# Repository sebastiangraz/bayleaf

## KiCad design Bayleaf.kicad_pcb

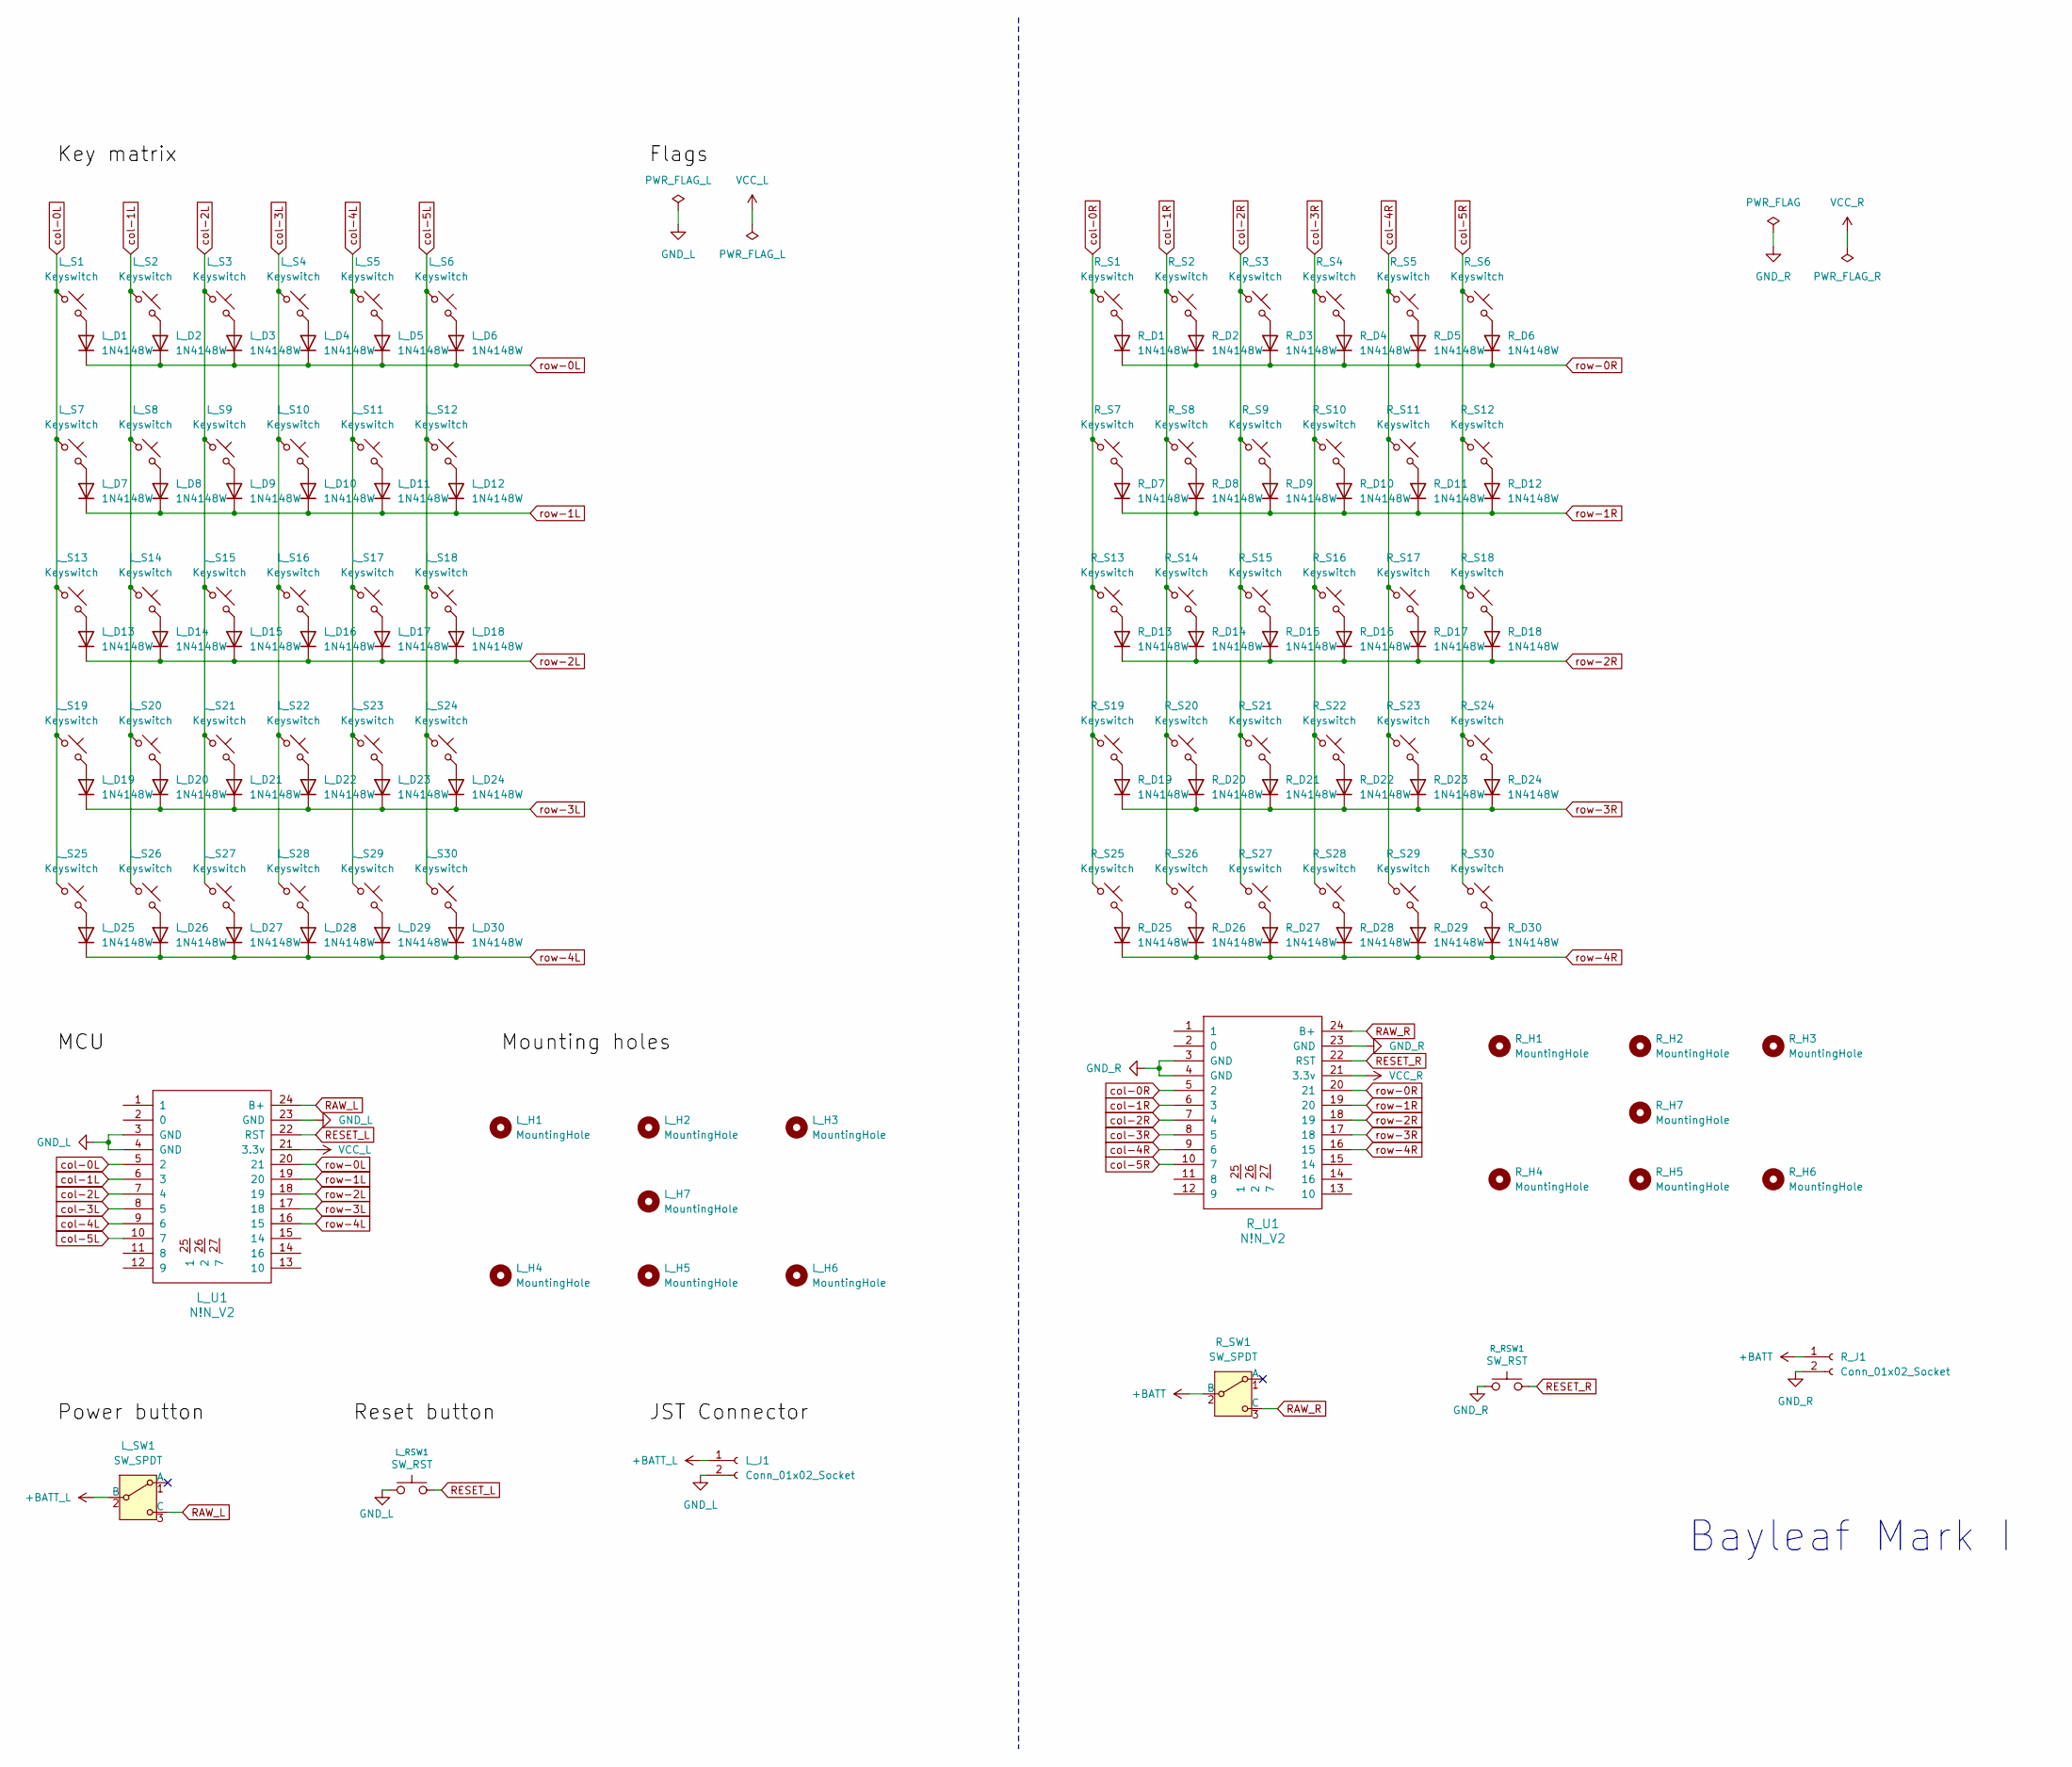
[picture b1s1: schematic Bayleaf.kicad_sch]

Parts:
L_D1, L_D2, L_D3, L_D4, L_D5, L_D6, L_D7, L_D8, L_D9, L_D10, L_D11, L_D12, L_D13, L_D14, L_D15, L_D16, L_D17, L_D18, L_D19, L_D20, L_D21, L_D22, L_D23, L_D24, L_D25, L_D26, L_D27, L_D28, L_D29, L_D30: 1N4148W; D_SOD-123
L_H1, L_H2, L_H3, L_H4, L_H5, L_H6, L_H7: MountingHole; MountingHole_2.2mm_M2
L_J1: Conn_01x02_Socket; JST_SH_SM02B-SRSS-TB_1x02-1MP_P1.00mm_Horizontal
L_RSW1: SW_RST; SW_Tactile_SPST_NO_Straight_CK_PTS636Sx25SMTRLFS
L_S1, L_S2, L_S3, L_S4, L_S5, L_S6, L_S7, L_S8, L_S9, L_S10, L_S11, L_S12, L_S13, L_S14, L_S15, L_S16, L_S17, L_S18, L_S19, L_S20, L_S21, L_S22, L_S23, L_S24, L_S25, L_S26, L_S27, L_S28, L_S29, L_S30: Keyswitch; CPG1316S01D02_mikeholscher
L_SW1: SW_SPDT; SW_SPDT_PCM12
L_U1: N!N_V2; Nice_Nano_V2
R_D1, R_D2, R_D3, R_D4, R_D5, R_D6, R_D7, R_D8, R_D9, R_D10, R_D11, R_D12, R_D13, R_D14, R_D15, R_D16, R_D17, R_D18, R_D19, R_D20, R_D21, R_D22, R_D23, R_D24, R_D25, R_D26, R_D27, R_D28, R_D29, R_D30: 1N4148W; D_SOD-123
R_H1, R_H2, R_H3, R_H4, R_H5, R_H6, R_H7: MountingHole; MountingHole_2.2mm_M2
R_J1: Conn_01x02_Socket; JST_SH_SM02B-SRSS-TB_1x02-1MP_P1.00mm_Horizontal
R_RSW1: SW_RST; SW_Tactile_SPST_NO_Straight_CK_PTS636Sx25SMTRLFS
R_S1, R_S2, R_S3, R_S4, R_S5, R_S6, R_S7, R_S8, R_S9, R_S10, R_S11, R_S12, R_S13, R_S14, R_S15, R_S16, R_S17, R_S18, R_S19, R_S20, R_S21, R_S22, R_S23, R_S24, R_S25, R_S26, R_S27, R_S28, R_S29, R_S30: Keyswitch; CPG1316S01D02_mikeholscher
R_SW1: SW_SPDT; SW_SPDT_PCM12
R_U1: N!N_V2; Nice_Nano_V2

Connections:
+BATT: R_J1.1, R_SW1.2 (B)
+BATT_L: L_J1.1, L_SW1.2 (B)
GND_L: L_J1.2, L_RSW1.1, L_U1.3 (GND), L_U1.4 (GND), L_U1.23 (GND)
GND_R: R_J1.2, R_RSW1.1, R_U1.3 (GND), R_U1.4 (GND), R_U1.23 (GND)
unnamed: L_D1.2 (A), L_S1.2
unnamed: L_D2.2 (A), L_S2.2
unnamed: L_D3.2 (A), L_S3.2
unnamed: L_D4.2 (A), L_S4.2
unnamed: L_D5.2 (A), L_S5.2
unnamed: L_D6.2 (A), L_S6.2
unnamed: L_D7.2 (A), L_S7.2
unnamed: L_D8.2 (A), L_S8.2
unnamed: L_D9.2 (A), L_S9.2
unnamed: L_D10.2 (A), L_S10.2
unnamed: L_D11.2 (A), L_S11.2
unnamed: L_D12.2 (A), L_S12.2
unnamed: L_D13.2 (A), L_S13.2
unnamed: L_D14.2 (A), L_S14.2
unnamed: L_D15.2 (A), L_S15.2
unnamed: L_D16.2 (A), L_S16.2
unnamed: L_D17.2 (A), L_S17.2
unnamed: L_D18.2 (A), L_S18.2
unnamed: L_D19.2 (A), L_S19.2
unnamed: L_D20.2 (A), L_S20.2
unnamed: L_D21.2 (A), L_S21.2
unnamed: L_D22.2 (A), L_S22.2
unnamed: L_D23.2 (A), L_S23.2
unnamed: L_D24.2 (A), L_S24.2
unnamed: L_D25.2 (A), L_S25.2
unnamed: L_D26.2 (A), L_S26.2
unnamed: L_D27.2 (A), L_S27.2
unnamed: L_D28.2 (A), L_S28.2
unnamed: L_D29.2 (A), L_S29.2
unnamed: L_D30.2 (A), L_S30.2
unnamed: R_D1.2 (A), R_S1.2
unnamed: R_D2.2 (A), R_S2.2
unnamed: R_D3.2 (A), R_S3.2
unnamed: R_D4.2 (A), R_S4.2
unnamed: R_D5.2 (A), R_S5.2
unnamed: R_D6.2 (A), R_S6.2
unnamed: R_D7.2 (A), R_S7.2
unnamed: R_D8.2 (A), R_S8.2
unnamed: R_D9.2 (A), R_S9.2
unnamed: R_D10.2 (A), R_S10.2
unnamed: R_D11.2 (A), R_S11.2
unnamed: R_D12.2 (A), R_S12.2
unnamed: R_D13.2 (A), R_S13.2
unnamed: R_D14.2 (A), R_S14.2
unnamed: R_D15.2 (A), R_S15.2
unnamed: R_D16.2 (A), R_S16.2
unnamed: R_D17.2 (A), R_S17.2
unnamed: R_D18.2 (A), R_S18.2
unnamed: R_D19.2 (A), R_S19.2
unnamed: R_D20.2 (A), R_S20.2
unnamed: R_D21.2 (A), R_S21.2
unnamed: R_D22.2 (A), R_S22.2
unnamed: R_D23.2 (A), R_S23.2
unnamed: R_D24.2 (A), R_S24.2
unnamed: R_D25.2 (A), R_S25.2
unnamed: R_D26.2 (A), R_S26.2
unnamed: R_D27.2 (A), R_S27.2
unnamed: R_D28.2 (A), R_S28.2
unnamed: R_D29.2 (A), R_S29.2
unnamed: R_D30.2 (A), R_S30.2
RAW_L: L_SW1.3 (C), L_U1.24 (B+)
RAW_R: R_SW1.3 (C), R_U1.24 (B+)
RESET_L: L_RSW1.2, L_U1.22 (RST)
RESET_R: R_RSW1.2, R_U1.22 (RST)
VCC_L: L_U1.21 (3.3v)
VCC_R: R_U1.21 (3.3v)
col-0L: L_S1.1, L_S7.1, L_S13.1, L_S19.1, L_S25.1, L_U1.5 (2)
col-0R: R_S1.1, R_S7.1, R_S13.1, R_S19.1, R_S25.1, R_U1.5 (2)
col-1L: L_S2.1, L_S8.1, L_S14.1, L_S20.1, L_S26.1, L_U1.6 (3)
col-1R: R_S2.1, R_S8.1, R_S14.1, R_S20.1, R_S26.1, R_U1.6 (3)
col-2L: L_S3.1, L_S9.1, L_S15.1, L_S21.1, L_S27.1, L_U1.7 (4)
col-2R: R_S3.1, R_S9.1, R_S15.1, R_S21.1, R_S27.1, R_U1.7 (4)
col-3L: L_S4.1, L_S10.1, L_S16.1, L_S22.1, L_S28.1, L_U1.8 (5)
col-3R: R_S4.1, R_S10.1, R_S16.1, R_S22.1, R_S28.1, R_U1.8 (5)
col-4L: L_S5.1, L_S11.1, L_S17.1, L_S23.1, L_S29.1, L_U1.9 (6)
col-4R: R_S5.1, R_S11.1, R_S17.1, R_S23.1, R_S29.1, R_U1.9 (6)
col-5L: L_S6.1, L_S12.1, L_S18.1, L_S24.1, L_S30.1, L_U1.10 (7)
col-5R: R_S6.1, R_S12.1, R_S18.1, R_S24.1, R_S30.1, R_U1.10 (7)
row-0L: L_D1.1 (K), L_D2.1 (K), L_D3.1 (K), L_D4.1 (K), L_D5.1 (K), L_D6.1 (K), L_U1.20 (21)
row-0R: R_D1.1 (K), R_D2.1 (K), R_D3.1 (K), R_D4.1 (K), R_D5.1 (K), R_D6.1 (K), R_U1.20 (21)
row-1L: L_D7.1 (K), L_D8.1 (K), L_D9.1 (K), L_D10.1 (K), L_D11.1 (K), L_D12.1 (K), L_U1.19 (20)
row-1R: R_D7.1 (K), R_D8.1 (K), R_D9.1 (K), R_D10.1 (K), R_D11.1 (K), R_D12.1 (K), R_U1.19 (20)
row-2L: L_D13.1 (K), L_D14.1 (K), L_D15.1 (K), L_D16.1 (K), L_D17.1 (K), L_D18.1 (K), L_U1.18 (19)
row-2R: R_D13.1 (K), R_D14.1 (K), R_D15.1 (K), R_D16.1 (K), R_D17.1 (K), R_D18.1 (K), R_U1.18 (19)
row-3L: L_D19.1 (K), L_D20.1 (K), L_D21.1 (K), L_D22.1 (K), L_D23.1 (K), L_D24.1 (K), L_U1.17 (18)
row-3R: R_D19.1 (K), R_D20.1 (K), R_D21.1 (K), R_D22.1 (K), R_D23.1 (K), R_D24.1 (K), R_U1.17 (18)
row-4L: L_D25.1 (K), L_D26.1 (K), L_D27.1 (K), L_D28.1 (K), L_D29.1 (K), L_D30.1 (K), L_U1.16 (15)
row-4R: R_D25.1 (K), R_D26.1 (K), R_D27.1 (K), R_D28.1 (K), R_D29.1 (K), R_D30.1 (K), R_U1.16 (15)

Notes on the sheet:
Bayleaf Mark I

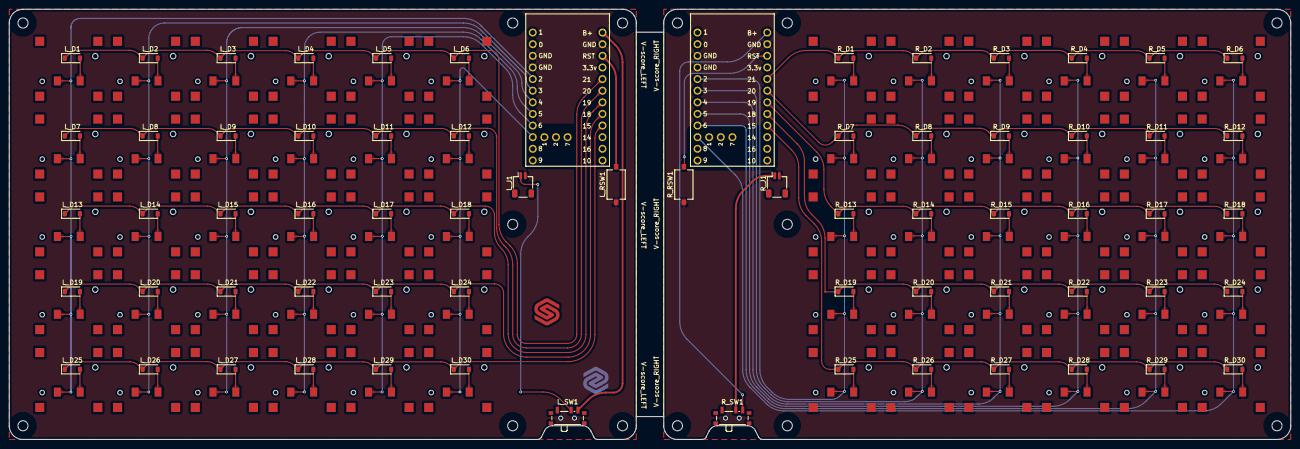
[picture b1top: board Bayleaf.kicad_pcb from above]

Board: 2 copper layers, 280.0 x 94.0 mm, 142 parts (0 on the bottom side), 90 nets.

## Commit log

2024-10-22 add kicad
2024-10-22 Add switch and cap
2024-10-23 v1 power management
2024-10-24 Added jst connector
2024-10-25 Add rst, flags, logo, mounting hole
2024-10-27 Add case params
2024-10-27 Add labels to sch
2024-10-27 org with assets folder
2024-10-27 V1 PCB, confirmed working state
2024-10-27 checkpoint before 1mm X resize
2024-10-28 images
2024-11-01 move sw
2024-11-05 Move components to fit under slope
2024-11-05 commit before adding 2nd half
2024-11-05 renamed schematic refs
2024-11-05 draft split labels schematic
2024-11-06 ref checkpoint
2024-11-06 Connect traces on right
2024-11-06 V1 production ready
2024-11-06 fix v-scoring
2024-11-06 fix v-score + edge zone fill fix
2024-11-06 backups
2024-11-07 production milestone
